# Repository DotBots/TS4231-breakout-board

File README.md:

# TS4231-breakout-board
Kicad hardware files for a breakout board of the TS4231 lighthouse v2 receiver IC from Triad Semiconductors. 
The PCB was designed to be as small as possible, and expose the 2 data lines from the TS4231 as well as VCC and GND

## Schematic

The schematic was taken directly from the recommended circuit from the TS4231 datasheet.

## PCB

## Bill of Materials
| Image | Function | Name | Quantity | Price per unit | Link |
|---|---|---|---|---|---|
|      | Lighthouse Receiver IC | TS4231 | 1 | $2.37 | [Buy](https://www.digikey.com/short/7jnj8fr2) |
|  | Photodiode 850nm 20ns 120° 2-SMD, Gull Wing | BPW 34 S-Z | 1 | $1.33 | [Buy](https://www.digikey.com/short/jhrrf52v) |
|     | 1 µF ±10% 16V Ceramic Capacitor X7R 0603 (1608 Metric) | CL10B105KO8NNNC | 1 | $0.1 | [Buy](https://www.digikey.com/short/j7tzj5fq) |
|   | 0.1 µF ±10% 16V Ceramic Capacitor X7R 0603 (1608 Metric) | CC0603KRX7R7BB104 | 1 | $0.1 | [Buy](https://www.digikey.com/short/vj2zz4q8) |
|    | 15 kOhms ±1% 0.1W, 1/10W Chip Resistor 0603 (1608 Metric) | ERJ-3EKF1502V | 1 | $0.1 | [Buy](https://www.digikey.com/short/5w9hm2pj) |

Total cost of components per unit: $4.0

## References
- TS4231 Datasheet: [Link](https://www.digikey.com/en/htmldatasheets/production/5835669/0/0/1/ts4231)
- Similar PCB project: [Link](https://hackaday.io/project/19570-htc-vive-lighthouse-custom-tracking/log/146239-ts4231)

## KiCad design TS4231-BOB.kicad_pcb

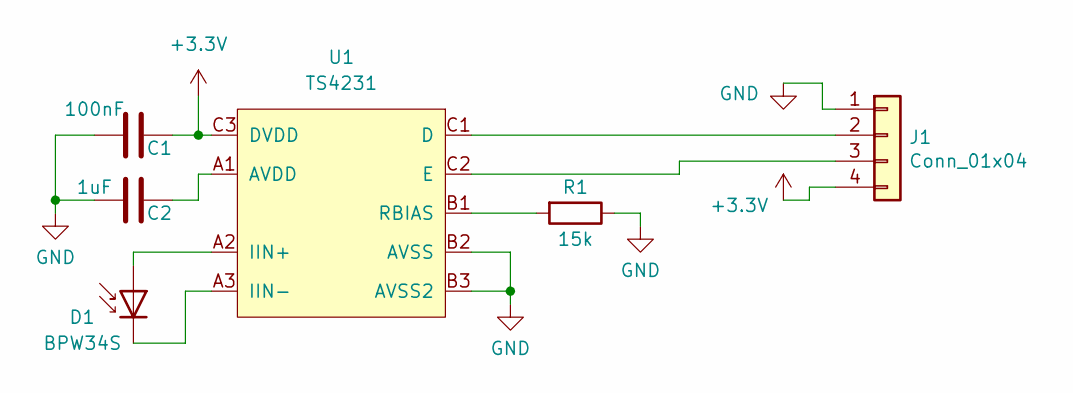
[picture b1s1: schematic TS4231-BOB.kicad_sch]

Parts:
C1: 100nF; C_0603_1608Metric; Mfr # CC0603KRX7R7BB104
C2: 1uF; C_0603_1608Metric; Mfr # CL10B105KO8NNNC
D1: BPW34S; BPW34; Mfr # BPW 34 S-Z
J1: Conn_01x04; PinHeader_1x04_P2.54mm_Vertical
R1: 15k; R_0603_1608Metric; Mfr # ERJ-3EKF1502V
U1: TS4231; Mfr # TS4231

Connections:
+3.3V: C1.1, J1.4, U1.C3 (DVDD)
GND: C1.2, C2.2, J1.1, R1.1, U1.B2 (AVSS), U1.B3 (AVSS2)
unnamed: D1.2 (A), U1.A2 (IIN+)
unnamed: D1.1 (K), U1.A3 (IIN-)
unnamed: J1.2, U1.C1 (D)
unnamed: J1.3, U1.C2 (E)
unnamed: C2.1, U1.A1 (AVDD)
unnamed: R1.2, U1.B1 (RBIAS)

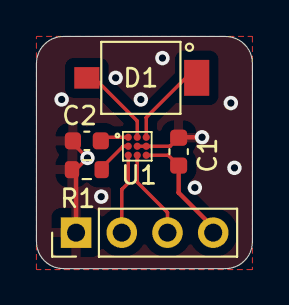
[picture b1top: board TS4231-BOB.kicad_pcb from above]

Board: 2 copper layers, 12.0 x 12.9 mm, 6 parts (0 on the bottom side), 8 nets.

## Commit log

2025-01-29 add BSD license
2025-01-29 add kicad project
2025-01-29 add gerber files
2025-01-29 update BOM
2025-01-29 Add readme
2025-01-29 update readme figure sizes
